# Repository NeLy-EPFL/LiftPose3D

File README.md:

# LiftPose3D

<!---  --->

LiftPose3D is a tool for transforming a 2D poses to 3D coordinates on labaratory animals. Classical approaches based on triangulation require synchronised acquisition from multiple cameras and elaborate calibration protocols. By contrast, LiftPose3D can reconstruct 3D poses from 2D poses from a single camera, in some instances without having to know the camera position or the type of lens used. For the theoretical background and details, have a look at our [paper](https://www.biorxiv.org/content/10.1101/2020.09.18.292680v1).

To train LiftPose3D, ideally you would need (A) a 3D pose library, (B) corresponding 2D poses from the camera that you will use for lifting and (C) camera matrices (extrinsic and intrinsic). 

If you do not have access to 
  * (A) then use one of the provided datasets,
  * (B) then obtain 2D images via projection using your camera matrices (you will need to calibrate to obtain these)
  * (C) then place your camera further away to assume weak perspective.

## Starting-Up
1. [Installation](https://github.com/NeLy-EPFL/LiftPose3D/blob/master/docs/install.md)
2. [LiftPose3D Paper](https://www.biorxiv.org/content/10.1101/2020.09.18.292680v1)
3. [Citing LiftPose3D](https://github.com/NeLy-EPFL/LiftPose3D/blob/master/docs/cite.md)

## Data format
During training, LiftPose3D accepts two numpy arrays in shape of `[N J 2]` and `[N J 3]` serving as input and output. Here, N is the number of poses and J is the number of joints. If you have multiple experiments, you can provide your data as dictionaries where the keys are strings and values are numpy arrays. You will also need the set at least one root joint and a set of target sets for each root joint. The network will predict the joints in the target sets relative to the root joints.

For each [example](https://github.com/NeLy-EPFL/LiftPose3D/tree/master/examples), we provide a unique `load.py` file to transform data into the required `[N J 3]` LifPose3D format.

## Training
You can train a network with the following generic syntax using experiment 1 for training and experiment 2 for testing.

  ```python
  from liftpose.main import train as lp3d_train
  import numpy.random.rand
  
  n_points, n_joints = 100, 5
  train_2d, test_2d = rand((n_points, n_joints, 2)), rand((n_points, n_joints, 2))
  train_3d, test_3d = rand((n_points, n_joints, 3)), rand((n_points, n_joints, 3))
  
  train_2d = {"experiment_1": train_2d}
  train_3d = {"experiment_1": train_3d}
  test_2d = {"experiment_2": test_2d}
  test_3d = {"experiment_2": test_3d}
  
  roots = [0]
  target_sets = [1,2,3,4]
  
  lp3d_train(train_2d, test_2d, train_3d, test_3d, roots, target_sets)
  ```

By default, the outputs will be saved in a folder `out` relative to the path where LiftPose3D is called. You can change this behavior using the `ouput_folder` parameter of the `train` function. You can take a look at the ```train``` function for other [default values and much longer documentation here](https://github.com/NeLy-EPFL/LiftPose3D/blob/e36d6598115c3eb7cf34f2ece90334df4200eee4/liftpose/main.py#L36).
  
For example, you can further configure training by passing an extra argument ```training_kwargs``` in ```train``` function.

  ```python
  from liftpose.main import train as lp3d_train
  training_kwargs={ "epochs": 15,                   # train for 15 epochs
                    "resume": True,                 # resume training where it was stopped
                    "load"  : 'ckpt_last.pth.tar'}, # use last training checkpoint to resume
                    
  lp3d_train(train_2d, test_2d, train_3d, test_3d, roots, target_sets, training_kwargs=training_kwargs)
  ```
  
You can overwrite all the parameter inside ```liftpose.lifter.opt``` using ```training_kwargs```.

## Training augmentation

Augmenting training data is a great way to account for variability in the dataset, especially when training data is scarce. 

Currently, available options in ```liftpose.lifter.augmentation``` are:
1. `add_noise`      : adding Gaussian noise on 2D training pose to account for uncertainty in test time
2. `random_project` : random projections of 3D pose in case camera orientation is unknown during test time (the training will ignore the input ```train_2d```)
3. `perturb_pose`   : pose augmentation by changing segment lengths when there are large animal-to-animal variation
4. `project_to_cam` : deterministic projections of 3D pose in case camera matrix is different and known in test time 

Training augmentation options can be specified in the argument `augmentation` and can be combined. 

  ```python
  from liftpose.main import train as lp3d_train
  from liftpose.lifter.augmentation import random_project
  
  angle_aug = {'eangles' : {0: [[-10,10], [-10, 10], [-10,10]]}, #range of Euler angles (dictionary indexed by an integer which specifies the camera identify)
               'axsorder': 'zyx', # order of rotations for euler angles
               'vis'     : None,  # used in case not all joints are visible from a given camera
               'tvec'    : None,  # camera translation vector
               'intr'    : None}  # camera intrinsic matrix
  
  aug = [random_project(**angle_aug)]
  lp3d_train(train_2d, test_2d, train_3d, test_3d, roots, target_sets, aug=aug)
  ```

See the case of [angle invariant Drosophila lifting](https://github.com/NeLy-EPFL/LiftPose3D/tree/master/examples/fly_tether_angle_inv) for an example implementation of augmentation.

## Inspecting the training  
  
  The training information is saved under the ```train_log.txt```, which can be visualized as follows.
  
  ```python
  from liftpose.plot import read_log_train, plot_log_train
  epoch, lr, loss_train, loss_test, err_test = read_log_train(par['out_dir'])
  plot_log_train(plt.gca(), loss_train, loss_test, epoch)
  ```
  This will plot the training and test losses during the training.

## Testing the network
  To test the network on the data provided during the ```lp3d_train``` call, run
  ```python
  from liftpose.main import test as lp3d_test
lp3d_test(par['out_dir'])
  ```
  Results will be saved inside the ```test_results.pth.tar``` file. 
  
  To test the network in new data, run
  
  ```python
  liftpose3d_test(par['out_dir'], test_2d, test_3d)
  ```
  where you provide the ```test_2d``` and ```test_3d``` in the format described above. This will overwrite the previous ```test_results.pkl``` file, if there is any.
  
  We also provide a simple interface for loading the test results from the ```test_results.pkl``` file. 
  
  ```python
  from liftpose.postprocess import load_test_results
  test_3d_gt, test_3d_pred, _ = load_test_results(par['out_dir'])
  ```
  This will return two numpy arrays: ```test_3d_gt```, which is the same as ```test_3d```, and ```test_3d_pred```, which has the predictions from the LiftPose3D.  
  
  To generate the error distribution run
 ```python
  from liftpose.plot import violin_plot
  
  names = ['Head', 'Nose', 'Shoulder',  'Hip',  'Knee', 'Foot', 'Hand']
  violin_plot(plt.gca(), test_3d_gt=test_3d_gt, test_3d_pred=test_3d_pred, test_keypoints=np.ones_like(test_3d_gt),
              joints_name=names, units='m', body_length=2.21)
  ```

## Visualizing the 3D pose

To visualize the output 3D pose, first specify an animal skeleton in the file ```params.yaml```. Note that bone information or the connected joints, are only used for visualization and not during training. You can have a closer look at ```plot_pose_3d``` function to see how the bone and color parameters are used during plotting. 

  ```params.yaml
  data:
      roots       : [0]
      target_sets : [[1, 2, 3, 4]]

  vis:
      colors      : [[186, 30, 49]]
      bones       : [[0, 1], [1, 2], [2, 3], [3, 4]]
      limb_id     : [0, 0, 0, 0, 0]
  ```
  
We provide the following function to visualize the 3D data

 ```python
from liftpose.plot import plot_pose_3d
fig = plt.figure(figsize=plt.figaspect(1), dpi=100)
ax = fig.add_subplot(111, projection='3d')
ax.view_init(elev=-75, azim=-90)

t = 0
plot_pose_3d(ax=ax, tar=test_3d_gt[t], 
            pred=test_3d_pred[t], 
            bones=par_data["vis"]["bones"], 
            limb_id=par_data["vis"]["limb_id"], 
            colors=par_data["vis"]["colors"],
            legend=True)
 ```
 This should output something similar to:

You can also easily create movies 

```python
from liftpose.plot import plot_video_3d

fig = plt.figure(figsize=plt.figaspect(1), dpi=100)
ax = fig.add_subplot(111, projection='3d')

ax.set_xlim([-4,2])
ax.set_ylim([-3,2])
ax.set_zlim([0,2])
    
plot_video_3d(fig, ax, n=gt.shape[0], par=par_data, tar=gt, pred=pred, trailing=10, trailing_keypts=[4,9,14,19,24,29], fps=20)
```

Use *trailing* to plot points *trailing_keypts* with a trailing effect with a desired length.

### Training with subset of points
In case you want to prevent some 2D/3D points from used in the training, you can pass ```train_keypts``` argument into the ```train``` function, which has the same shape as ```train_3d``` but has boolean datatype. Alternatively, in case you have missing keypoints, you can convert them to ```np.NaN```. In both cases, the loss from these points is not going to be used during backpropagation.

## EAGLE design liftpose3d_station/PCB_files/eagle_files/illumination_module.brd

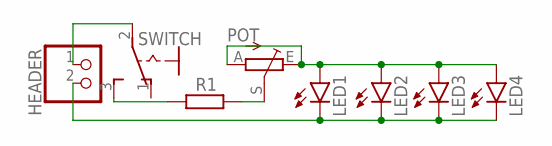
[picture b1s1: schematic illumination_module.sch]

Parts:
HEADER: PINHD-1X2/90; 1X02/90
LED1, LED2, LED3, LED4: LED5MM
POT: TRIM_EU-CA6H; CA6H
R1: R-EU_0207/10; 0207/10
SWITCH: 255SB

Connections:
unnamed: LED1.A, LED2.A, LED3.A, LED4.A, POT.A, POT.E
unnamed: R1.1, SWITCH.3 (S)
unnamed: HEADER.2, LED1.K (C), LED2.K (C), LED3.K (C), LED4.K (C)
unnamed: POT.S, R1.2
unnamed: HEADER.1, SWITCH.2

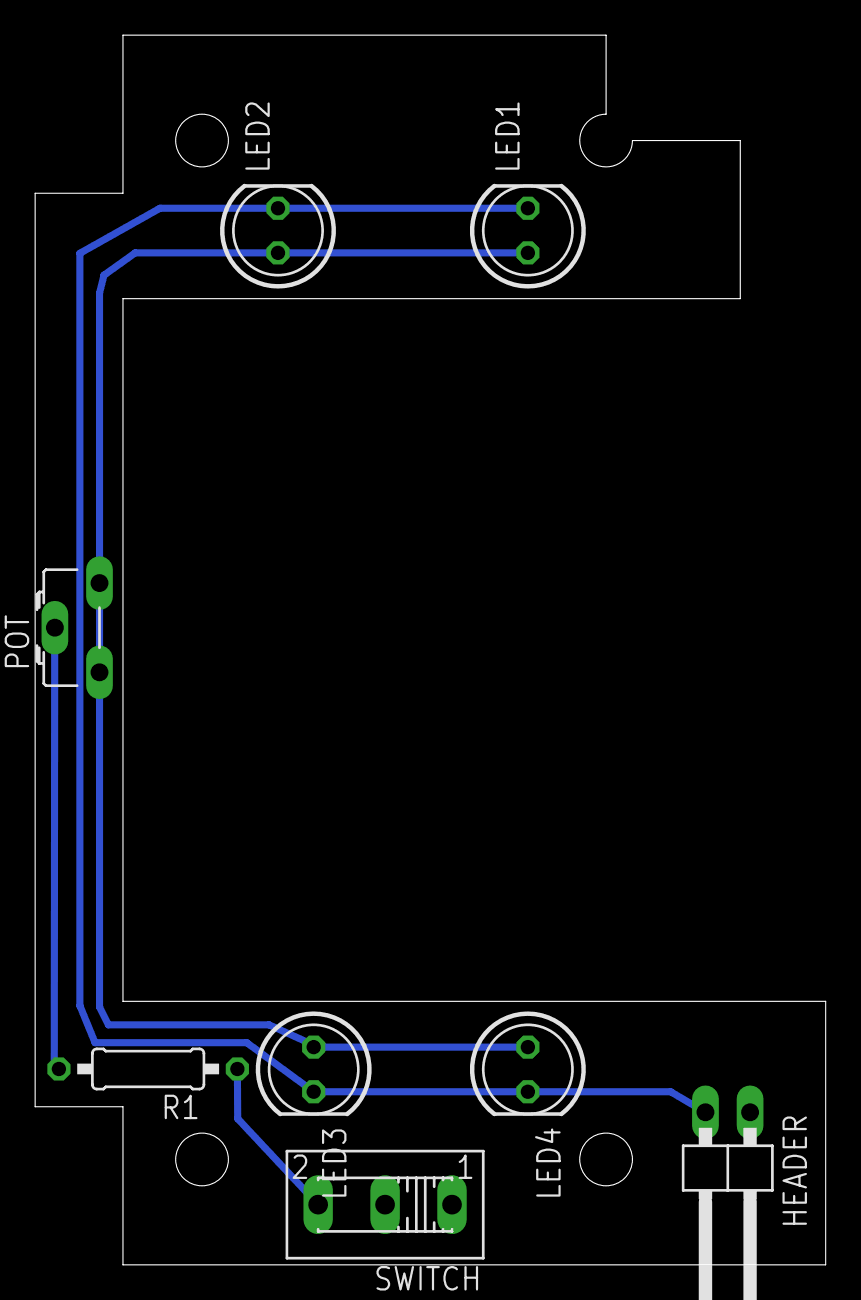
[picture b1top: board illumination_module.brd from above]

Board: 2 copper layers, 45.0 x 70.0 mm, 8 parts (0 on the bottom side), 5 nets.

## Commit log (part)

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2020-07-29 not final version
2020-07-31 parameter file
2020-07-31 merged optobot code with prism code
2020-08-03 refine optobot
2020-08-13 final DF3D + prism
2020-08-14 optobot ok
2020-08-23 mouse
2020-08-28 flylimbtracker OK
2020-08-31 all working
2020-09-01 code cleanup
2020-09-04 final, but still try to uniformize code
2020-09-06 adding monkey
2020-09-07 readme and harmonization
2020-09-07 remove old stuff
2020-09-10 update readme, add images
2020-09-10 new images
2020-09-30 small bugfix
2020-10-13 detection [#1]
2020-10-13 detection up side and ventral views added
2020-10-19 cropping and contrast added [#2]
2020-10-19 video and height pad added
2020-10-20 stable: video for DLC
2020-10-20 correct typo
2020-10-20 bug fix
2020-10-20 stable: video for DLC [#2]
2020-10-20 stable: video for DLC [#3]
2020-11-10 fly 1 and 5 added
2020-11-19 developing..
2020-11-20 rotation back the VV
2020-11-20 saving points3d.npy
2020-11-24 point3d animation added.
2020-11-25 code added
2020-11-26 3D ANIMATIONS ADDED
2020-12-02 latest so far
2020-12-02 points3d added
2020-12-06 adding AniPose switch
2020-12-06 adding AniPose switch [#2]
2020-12-06 add AniPose switch [#3]
2020-12-09 filtered Anipose
2020-12-15 names corrected
2020-12-16 developing
2020-12-19 adding package init
2020-12-20 adding logger, adding lifter training
2020-12-20 adding test method; starting visualization
2020-12-20 update tether notebook
2020-12-21 deleting unnecessary files
2020-12-21 deleting liftpose2d_src folder
2020-12-21 remove unnecessary files under fly_tether
2020-12-21 remove src folder fly_tether
2020-12-21 removing src folder fly_tether
2020-12-21 cleaning fly_tether load
2020-12-21 update fly tether
2020-12-25 adding fly_prism
2020-12-25 removing fly_prism out
2020-12-25 deleting old examples
2020-12-25 adding mouse prism
2020-12-25 update notebooks
2020-12-26 fix 3 examples
2020-12-26 better api, accepts 3d points. remove unnecessary arguments. start fly_highres. work on predict flag
2020-12-30 adding windows path support; adding environment.ymll
2020-12-30 adding cpu support
2020-12-30 adding more documentation
2020-12-31 adding more comments
2021-01-03 starting openmonkey
2021-01-03 update examples
2021-01-10 updating monkey example
2021-01-15 remaining reforms
2021-01-15 commit with token
2021-01-15 modified latest
2021-01-16 new readme installation instructions
2021-01-18 toDOs added
2021-01-20 concatenate added
2021-01-24 adding capture
2021-01-25 capture
2021-01-25 universal lifter
2021-01-31 working tether and prism
2021-02-01 latest manual label correction and interpolation
2021-02-02 latest manual label correction and interpolation #2
2021-02-04 fixing
2021-02-04 reprojection error
2021-02-04 plotting docstrings
2021-02-05 adding network args
2021-02-06 adding augmentations
2021-02-08 adding normalize bone length; fixing violin plot
2021-02-08 concatenation+linear interpolation of wing grooming for NeuroMechFly
2021-02-09 domain_adaptation
2021-02-10 adding projection augmentation
2021-02-10 remove the debugging break
2021-02-15 refining abdomen grooming
2021-02-16 cropping window for fly_2 AG 4 corrected
2021-02-16 bug fix with computing mean
2021-02-16 universal_lifter
2021-02-17 root points are good keypoints; adding bone length normalization; setting test set after training
2021-02-17 roots are good keypoints
2021-02-17 adding bone-normalization comment
2021-02-17 changing variable names in preprocess
2021-02-17 fix replace nan error in preprocess
2021-02-17 remove nans
2021-02-17 angle_invariant
2021-02-18 debug
2021-02-18 bug fix in normalization
2021-02-18 errors for angle-inv lifter
2021-02-19 update capture notebook
2021-02-19 remove debug line
2021-02-21 update capture; add procrustes
2021-02-23 adding plot_video_3d
2021-02-26 universal lifter, pose norm, removed intr, tvec
2021-02-26 capture data with angle augmentation
2021-02-27 pose augmentation
2021-02-27 last status for the longest anterior grooming
2021-02-28 angle_invariant lifter errors
2021-03-01 angle augmentation
2021-03-01 reproduce fly_tether; adding procrustes; finalize test new data
2021-03-01 update mouse_prism
2021-03-01 update mouse_prism to reproduce
2021-03-01 adding new monkey train
2021-03-01 adding figure2g stats utils
2021-03-01 Update environment.yml
    updating environment.yml
2021-03-01 ignore run time warning mean of empty slice
2021-03-01 getting rid of warnings
2021-03-01 done angle-invariant lifter
2021-03-02 fly tether errors
2021-03-02 capture results
2021-03-03 remove head
2021-03-03 making invariant work
2021-03-03 fixing capture path
2021-03-05 update environment&setup
2021-03-05 adding install
2021-03-06 add figure_2e
2021-03-06 adding video code;openmonkey update;plot mae;
2021-03-07 adding fly ventral highres video
2021-03-08 update video code
2021-03-09 clean + fixes
2021-03-09 fix procrustes
2021-03-09 add monkey video
2021-03-09 removing monkey.ipynb
2021-03-09 update monkey
2021-03-09 adding fly_prism training and plot
2021-03-09 new monkey make video
2021-03-09 removing utils and stats
2021-03-09 remove monkey.ipynb
2021-03-09 adding legacy
2021-03-09 monkey
2021-03-09 adding mouse_prism
2021-03-09 editing fly_tether
2021-03-09 add legacy fly prism skeleton
2021-03-09 init figure1g
2021-03-09 update fly_tether
2021-03-09 update monkey_video
2021-03-09 update mouse prism
2021-03-09 update environment
2021-03-10 fly_tether
2021-03-10 adding readme's
2021-03-10 fly_prism reaadme
2021-03-11 fly_tether ok, legacy removed
2021-03-11 angle_invariant ok
2021-03-11 capture ok
2021-03-11 fly_prism ok
2021-03-25 domain adaptation
2021-03-26 cleanup
2021-03-26 small bug in augmentation
2021-03-26 small bug in mouse
2021-03-29 Revert "clean + fixes"
    This reverts commit 3bbd378beb45778b0a6b8ad7f8d17bd974321822.
2021-03-30 adding monkey object
2021-03-31 Create LICENSE
2021-04-02 bug fixes
2021-04-03 plot bug fix
2021-04-03 domain adaptation videos
2021-04-06 Rename train_fly_prism_network.ipynb to train_network.ipynb
2021-04-08 fix typo on desc; increase version
2021-04-08 adding missing liftpose.lifter package on setup.py
2021-05-26 Adding liftpose3d station files
2022-07-28 Update augmentation.py
    bug fix, did not pass the raw data
